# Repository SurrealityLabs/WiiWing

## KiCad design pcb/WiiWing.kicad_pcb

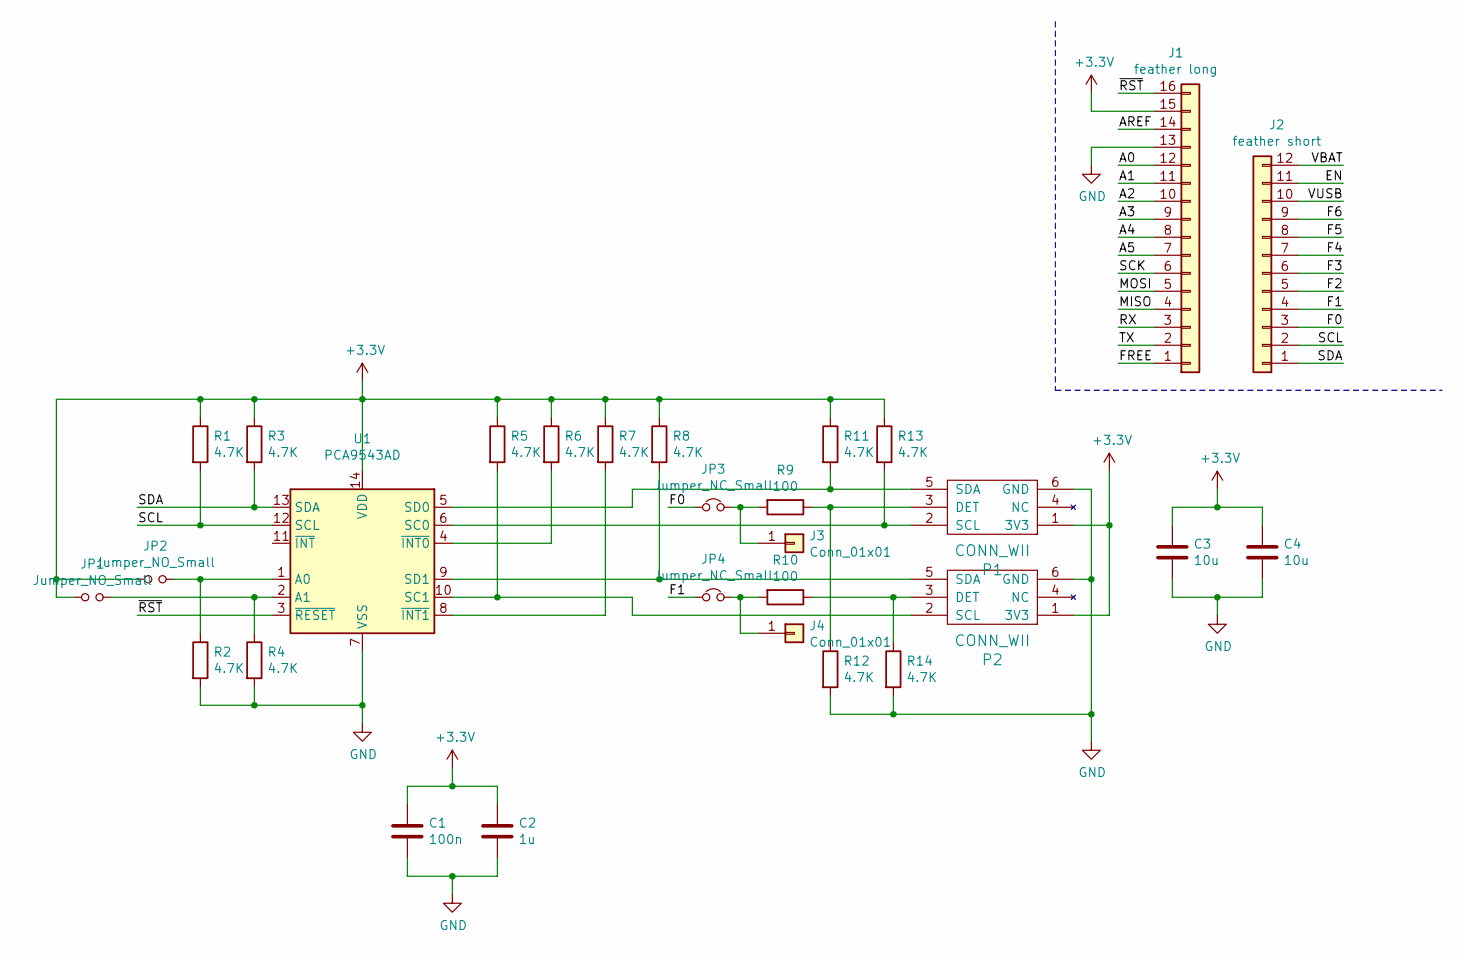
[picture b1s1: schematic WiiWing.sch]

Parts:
C1: 100n; C_0603_1608Metric
C2: 1u; C_0603_1608Metric
C3, C4: 10u; C_0805_2012Metric
J1: feather long; PinHeader_1x16_P2.54mm_Vertical
J2: feather short; PinHeader_1x12_P2.54mm_Vertical
J3, J4: Conn_01x01; PinHeader_1x01_P2.54mm_Vertical
JP1, JP2: Jumper_NO_Small; SolderJumper-2_P1.3mm_Open_Pad1.0x1.5mm
JP3, JP4: Jumper_NC_Small; SolderJumper-2_P1.3mm_Bridged_Pad1.0x1.5mm
P1, P2: CONN_WII
R1, R2, R3, R4, R5, R6, R7, R8, R11, R12, R13, R14: 4.7K; R_0603_1608Metric
R9, R10: 100; R_0603_1608Metric
U1: PCA9543AD; SOIC-14_3.9x8.7mm_P1.27mm

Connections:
+3V3: C1.1, C2.1, C3.1, C4.1, J1.15, JP1.1, JP2.1, P1.1 (3V3), P2.1 (3V3), R1.1, R3.1, R5.1, R6.1, R7.1, R8.1, R11.1, R13.1, U1.14 (VDD)
/A0: J1.12
/A1: J1.11
/A2: J1.10
/A3: J1.9
/A4: J1.8
/A5: J1.7
/AREF: J1.14
/EN: J2.11
/F0: J2.3, JP3.1
/F1: J2.4, JP4.1
/F2: J2.5
/F3: J2.6
/F4: J2.7
/F5: J2.8
/F6: J2.9
/FREE: J1.1
/MISO: J1.4
/MOSI: J1.5
/RX: J1.3
/SCK: J1.6
/SCL: J2.2, R1.2, U1.12 (SCL)
/SDA: J2.1, R3.2, U1.13 (SDA)
/TX: J1.2
/VBAT: J2.12
/VUSB: J2.10
/~RST: J1.16, U1.3 (~RESET)
GND: C1.2, C2.2, C3.2, C4.2, J1.13, P1.6 (GND), P2.6 (GND), R2.2, R4.2, R12.2, R14.2, U1.7 (VSS)
unnamed: J3.1, JP3.2, R9.2
unnamed: J4.1, JP4.2, R10.2
unnamed: JP1.2, R4.1, U1.2 (A1)
unnamed: JP2.2, R2.1, U1.1 (A0)
unnamed: P1.2 (SCL), R13.2, U1.6 (SC0)
unnamed: P1.3 (DET), R9.1, R12.1
unnamed: P1.5 (SDA), R11.2, U1.5 (SD0)
unnamed: P2.2 (SCL), R5.2, U1.10 (SC1)
unnamed: P2.3 (DET), R10.1, R14.1
unnamed: P2.5 (SDA), R8.2, U1.9 (SD1)
unnamed: R6.2, U1.4 (~INT0)
unnamed: R7.2, U1.8 (~INT1)

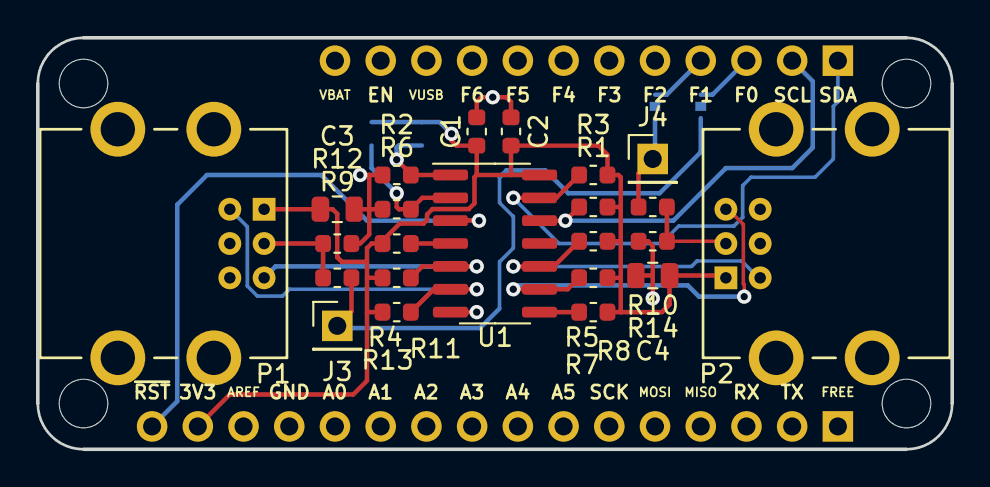
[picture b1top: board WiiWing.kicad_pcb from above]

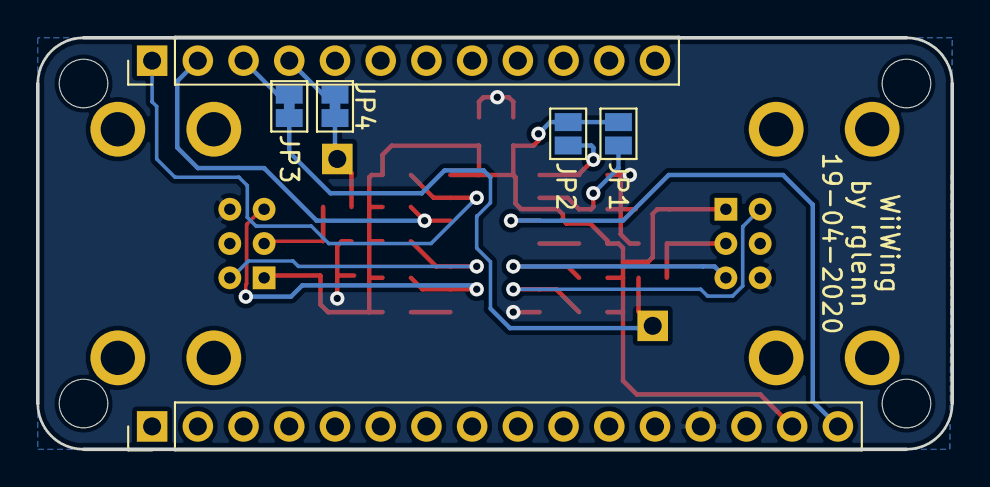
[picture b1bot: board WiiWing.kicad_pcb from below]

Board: 2 copper layers, 50.8 x 22.9 mm, 29 parts (6 on the bottom side), 19 nets.

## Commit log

2020-04-20 Adding first rev of PCB
